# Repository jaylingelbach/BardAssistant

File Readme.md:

# BardAssistant – The Bard’s Assistant (ESP32-S3)

A tiny “Vicious Mockery” companion built on an ESP32-S3 DevKitM-1.

Right now it:

- Uses **buttons** to request insults (`Random`, `Next`, `Prev`, `Sleep (hold)`).
- Uses a **NeoPixel** as a simple state indicator:
  - **Blue** – Booting
  - **Green** – Idle (ready for button presses)
  - **Yellow** – Updating (pretending to “do work”)
  - **Magenta ** – Updating
- Prints insults and status info over **Serial** (`115200` baud).

Planned:

- Add a **Waveshare 2.13" E-Ink** screen and render insults + header there.
- Power stuff / sleep / wake on long-press.

---

## Hardware

Current setup:

- **Board**: ESP32-S3 DevKitM-1
- **LED**:
  - 1x NeoPixel RGB LED
  - Data pin: `GPIO 21`
- **Buttons** (tactile switches to GND, using `INPUT_PULLUP` in code):
  - Random: `GPIO 4`
  - Next: `GPIO 5`
  - Prev: `GPIO 6`
  - Sleep: `GPIO 7`

Planned display (not wired/used yet):

- Waveshare 2.13" E-Ink Display HAT V4
  - 250x122, SPI, partial refresh
  - Will eventually show:
    - Title screen / logo
    - Current insult text
    - Basic “source” info (`Random / Next / Prev`)

---

## Firmware Overview

All of this lives in `src/main.cpp` for now, plus small modules:

- `lib/button/` – debounced button input
- `lib/led/` – NeoPixel status LED

### Application States

```cpp
enum class ApplicationState { Boot, Idle, Updating };
```

- **Boot**
  - LED: Blue (`ledShowBoot()`)
  - After ~2 seconds, transitions to **Idle**

- **Idle**
  - LED: Green (`ledShowIdle()`)
  - Listens for button taps:
    - Random → start a “Random insult” operation
    - Next → move forward through insult history (or draw new)
    - Prev → move backward through insult history

- **Updating**
  - LED: Yellow (`ledShowUpdating()`)
  - Simulates “work” with a small delay (`MOCK_WORK_MS`)
  - When “done”, applies the insult index and goes back to Idle

### Buttons & Events

Buttons are debounced and produce high-level events (from `button` module):

```cpp
enum class ButtonEvent { None, Tap, HoldStart, HoldEnd };
```

- Tap → triggers Random / Next / Prev operations _while in Idle_
- Sleep:
  - `HoldStart` is wired to eventually trigger deep sleep (`enterSleep()`),
    currently just logs.

### Insults, Deck, and History (Serial Only for Now)

- `insults[]` – array of `const char*` insult strings.
- **Deck**:
  - Shuffled list of indices, ensures “Random” doesn’t repeat until all have been used.

- **History**:
  - Remembers which insults have been shown.
  - `Next` / `Prev` navigate the history when possible.
  - `Next` at the end of history draws a new insult from the deck.

Rendering is currently:

- `renderTitleScreen()` – ASCII art + project name on boot (Serial only).
- `renderInsultAtIndex(...)` – logs:
  - Which insult index is active
  - The insult text itself
  - Optional context (`Random` vs `Next` vs `Prev`)

Later, these will be redirected to the E-Ink screen instead of (or in addition to) Serial.

---

## PlatformIO – Commands I Keep Forgetting

> All commands assume you’re in the project root (where `platformio.ini` lives).

### Build

**Generic:**

```bash
pio run
```

**Specific environment (ESP32-S3 DevKitM-1):**

```bash
pio run -e esp32-s3-devkitm-1
```

---

### Upload Firmware

**Generic upload for default env:**

```bash
pio run -t upload
```

**Upload to ESP32-S3 DevKitM-1 explicitly:**

```bash
pio run -e esp32-s3-devkitm-1 -t upload
```

---

### Erase Flash

Useful when things get weird or after changing flash layout / partitions:

```bash
pio run -e esp32-s3-devkitm-1 -t erase
```

Then re-upload your firmware.

---

### Clean Build Artifacts

If builds start acting cursed:

```bash
pio run -t clean
```

---

### Serial Monitor

**On my Mac / current setup:**

```bash
pio device monitor -p /dev/cu.usbmodem1101 -b 115200
```

Generic form:

```bash
pio device monitor -p <PORT> -b 115200
```

Hit `Ctrl + C` to exit.

---

## Development Notes

- Buttons are wired **to GND** and use `INPUT_PULLUP`:
  - Released → HIGH
  - Pressed → LOW

- Long-press on Sleep is **debounced and recognized**.
- State machine and insult logic are conceptually separate:
  - `main.cpp` handles:
    - Board setup
    - State transitions
    - Calling “work engine” functions

- Insult/deck/history logic lives in `lib/insults/`

---

## Sleep / Wake Behavior

### Entering Sleep

1. **Hold** the Sleep button to arm sleep mode (LED turns magenta).
2. **Release** the button to enter deep sleep.

This "hold to sleep, release to confirm" gesture prevents accidental sleep entry.

### Waking Up

1. **Tap** or **press** the Sleep button while asleep — the pin goes LOW and triggers a wake.
2. The ESP32-S3 boots from reset and runs `setup()` again.
3. Optionally, wake reason can be detected via `esp_sleep_get_wakeup_cause()`.

## Setup (Fresh Clone)

```bash
# Clone
git clone https://github.com/jaylingelbach/BardAssistant.git
cd BardAssistant

# Build (default env)
pio run

# Or build for the ESP32-S3 env explicitly
pio run -e esp32-s3-devkitm-1

# Upload
pio run -e esp32-s3-devkitm-1 -t upload

# Monitor
pio device monitor -p /dev/cu.usbmodem1101 -b 115200
```

## Current display panel being used

- GxEPD2_213_B74

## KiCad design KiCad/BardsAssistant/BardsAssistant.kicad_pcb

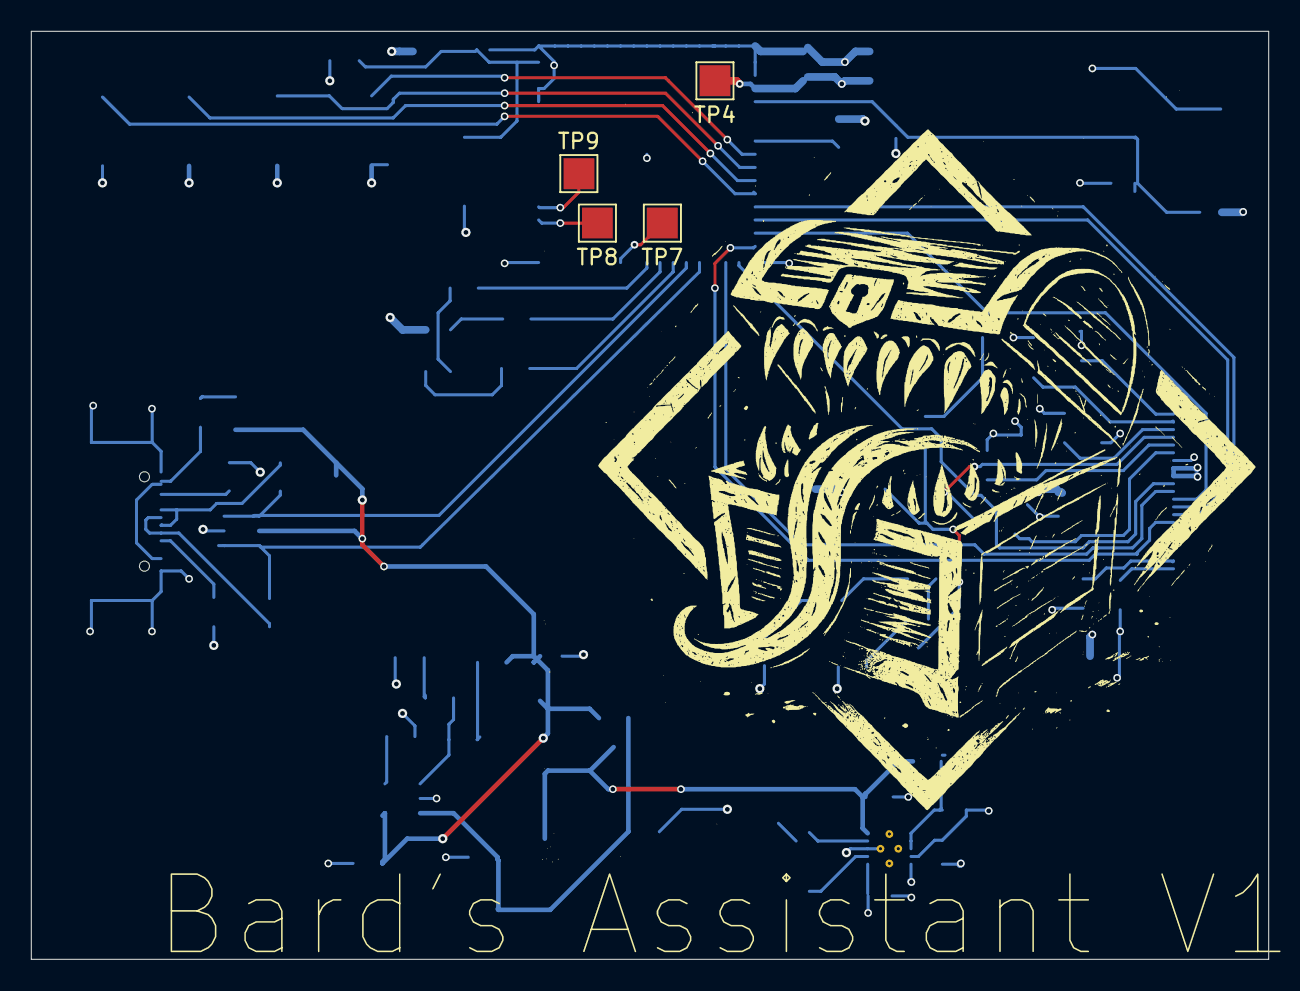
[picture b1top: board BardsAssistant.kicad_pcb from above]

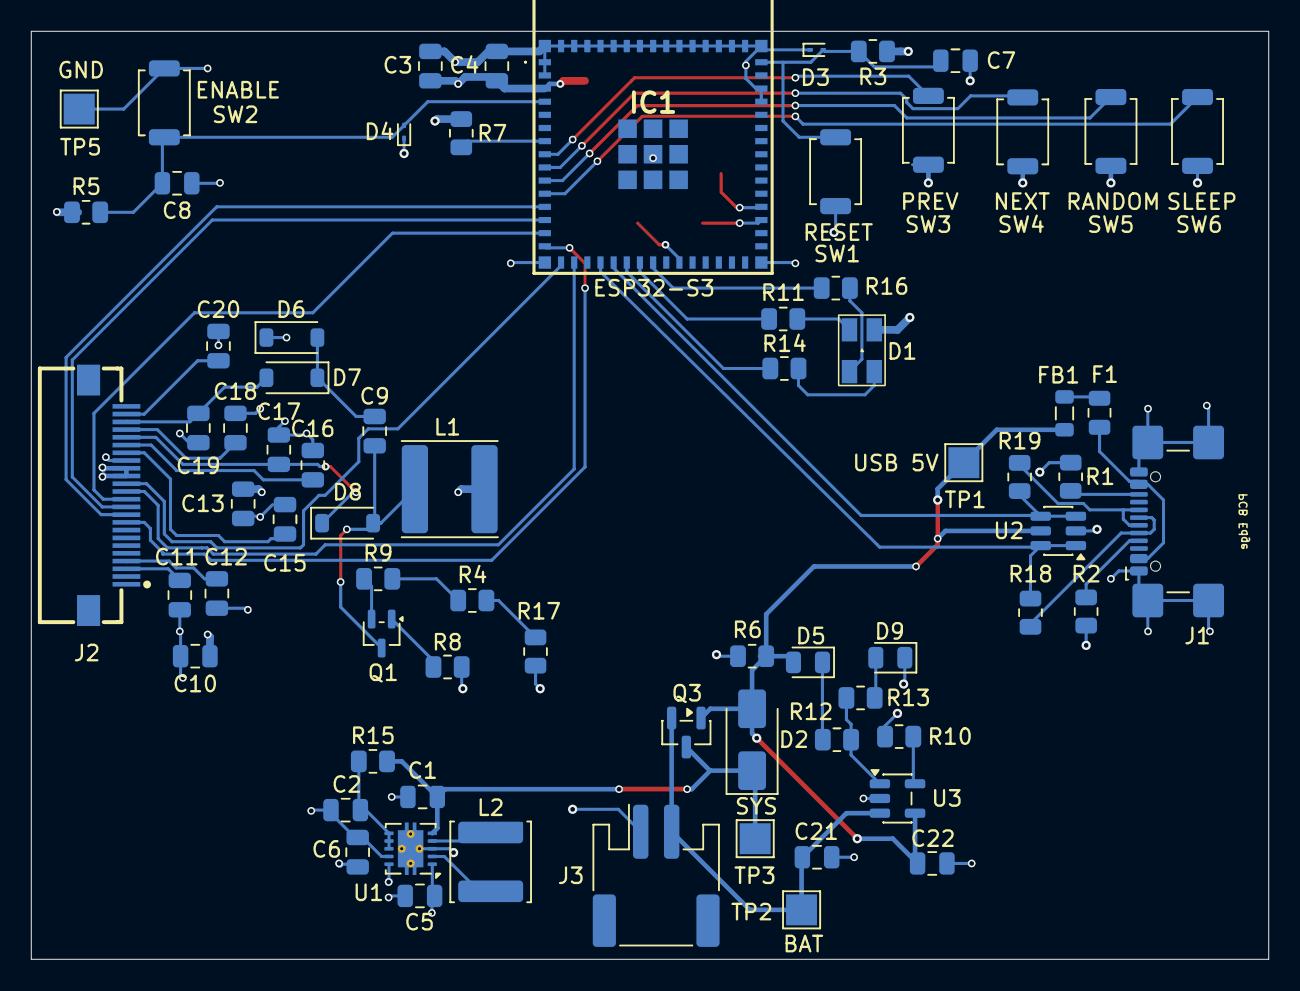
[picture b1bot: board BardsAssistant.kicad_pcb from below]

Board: 4 copper layers, 80.0 x 60.0 mm, 76 parts (72 on the bottom side), 56 nets.

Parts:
C1, C5, C6, C21, C22: 10uF; C_0805_2012Metric
C2, C4: .1uF; C_0805_2012Metric
C3: 22uF; C_0805_2012Metric
C7, C8, C11, C12, C13, C15, C16, C17, C18, C19, C20: 1uF; C_0805_2012Metric
C9, C10: 4.7uF; C_0805_2012Metric
D1: SM1210RGB; LED_XL-3227RGB-RF
D2: SS114; D_SMA
D3, D4: ESD9B3.3; D_SOD-923
D5: LED Red; LED_0805_2012Metric
D6, D7, D8: MBR0530; D_SOD-123
D9: LED Green; LED_0805_2012Metric
F1: Polyfuse 1A; Fuse_0805_2012Metric
FB1: BLM21PG221; L_0805_2012Metric
IC1: ESP32-S3-MINI-1-N8; ESP32S3MINI1N8
J1: USB_C_Receptacle_USB2.0_16P; USB_C_Receptacle_GCT_USB4110
J2: Conn_01x24; FPC-SMD_KH-FG0.5-H2.0-24PIN
J3: JST-PH-2-SMT-RA; JST_PH_S2B-PH-SM4-TB_1x02-1MP_P2.00mm_Horizontal
L1: 68uH; L_Sunlord_SWPA6045S
L2: 2.2uH; SMNR5040_2R2MT_BA
Q1: Si1308EDL; SOT-323_SC-70
Q3: AO3401A; SOT-23
R1, R2, R10: 5K1; R_0805_2012Metric
R3, R5, R7, R8: 10K; R_0805_2012Metric
R4, R9, R17: 1R; R_0805_2012Metric
R6: 100K; R_0805_2012Metric
R11, R14, R16: 330R; R_0805_2012Metric
R12, R13: 470R; R_0805_2012Metric
R15: 100R; R_0805_2012Metric
R18, R19: 22R; R_0805_2012Metric
SW1, SW2, SW3, SW4, SW5, SW6: SW_Push; SW_SPST_TS-1088-xR020
TP1, TP2, TP3, TP4, TP7, TP8, TP9: TestPoint; TestPoint_Pad_2.0x2.0mm
TP5: GND; TestPoint_Pad_2.0x2.0mm
U1: TPS63001; Texas_DRC0010J_ThermalVias
U2: USBLC6-2SC6; SOT-23-6
U3: MCP73831/2; SOT-23-5

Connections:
+3V3: C3.1, C4.1, C5.2, C6.2, C10.2, C13.2, D1.1 (A), IC1.3 (3V3), J2.15 (VDDIO), J2.16 (VCI), L1.1, R3.1, R5.1, R7.1, TP4.1, U1.1 (VOUT), U1.10 (FB)
/BAT: C21.2, J3.2, Q3.2 (BAT), TP2.1, U3.3 (V_{BAT})
/BUSY: IC1.15 (IO11), J2.9 (BUSY)
/CS: IC1.14 (IO10), J2.12 (CS)
/D+: IC1.20 (IO16), R19.1, U2.3 (I/O2), U2.4 (I/O2)
/D-: IC1.19 (IO15), R18.1, U2.1 (I/O1), U2.6 (I/O1)
/DC: IC1.13 (IO9), J2.11 (D/C)
/GDR: Q1.1 (G), R8.2
/MOSI: IC1.16 (IO12), J2.14 (SDI)
/PREVGH: C17.2, D8.1 (K), J2.20 (VSH)
/PREVGL: C19.2, D7.2 (A), J2.22 (VSL)
/RESE: Q1.2 (S), R9.1
/RST: IC1.12 (IO8), J2.10 (RST)
/SCK: IC1.17 (IO13), J2.13 (SCLK)
/SYS: C1.2, D2.1 (K), Q3.3 (SYS), R15.2, TP3.1, U1.5 (VIN)
/USB_5V: C22.2, D2.2 (A), D5.2 (A), FB1.2, Q3.1 (G), R6.2, TP1.1, U2.5 (VBUS), U3.4 (V_{DD})
GND: C1.1, C2.1, C3.2, C4.2, C5.1, C6.1, C7.2, C8.2, C10.1, C11.1, C12.1, C13.1, C15.1, C16.1, C17.1, C18.1, C19.1, C20.1, C21.1, C22.1, D3.1 (A1), D4.1 (A1), D6.1 (K), D9.1 (K), IC1.1 (GND_1), IC1.2 (GND_2), IC1.42 (GND_3), IC1.43 (GND_4), IC1.46 (GND_5), IC1.47 (GND_6), IC1.48 (GND_7), IC1.49 (GND_8), IC1.50 (GND_9), IC1.51 (GND_10), IC1.52 (GND_11), IC1.53 (GND_12), IC1.54 (GND_13), IC1.55 (GND_14), IC1.56 (GND_15), IC1.57 (GND_16), IC1.58 (GND_17), IC1.59 (GND_18), IC1.60 (GND_19), IC1.61 (GND_20), IC1.62 (GND_21), IC1.63 (GND_22), IC1.64 (GND_23), IC1.65 (GND_24), J1.A1 (GND), J1.A12 (GND), J1.B1 (GND), J1.B12 (GND), J1.S1 (SHIELD), J2.17 (VSS), J3.1, R1.1, R2.1, R6.1, R8.1, R10.2, R17.2, SW1.2, SW2.2, SW3.2, SW4.2, SW5.2, SW6.2, TP5.1, U1.3 (PGND), U1.9 (GND), U1.11 (PGND), U2.2 (GND), U3.2 (V_{SS})
unnamed: D1.4 (BK), R16.1
unnamed: D1.3 (GK), R14.1
unnamed: D1.2 (RK), R11.1
unnamed: C7.1, D3.2 (A2), IC1.45 (EN), R3.2, SW1.1
unnamed: C8.1, D4.2 (A2), IC1.4 (IO0), R5.2, SW2.1
unnamed: D5.1 (K), R12.1
unnamed: C9.1, D6.2 (A), D7.1 (K)
unnamed: C9.2, D8.2 (A), L1.2, Q1.3 (D)
unnamed: D9.2 (A), R13.1
unnamed: F1.1, J1.A4 (VBUS), J1.A9 (VBUS), J1.B4 (VBUS), J1.B9 (VBUS)
unnamed: F1.2, FB1.1
unnamed: IC1.7 (IO3), R7.2
unnamed: IC1.8 (IO4), SW3.1
unnamed: IC1.9 (IO5), SW4.1
unnamed: IC1.10 (IO6), SW5.1
unnamed: IC1.11 (IO7), SW6.1
unnamed: IC1.21 (IO17), R14.2
unnamed: IC1.22 (IO18), R11.2
unnamed: IC1.23 (IO19), R16.2
unnamed: IC1.25 (IO21), TP7.1
unnamed: IC1.33 (IO37), TP8.1
unnamed: IC1.34 (IO38), TP9.1
unnamed: J1.A5 (CC1), R2.2
unnamed: J1.B5 (CC2), R1.2
unnamed: J1.A6 (D+), J1.B6 (D+), R19.2
unnamed: J1.A7 (D-), J1.B7 (D-), R18.2
unnamed: C18.2, J2.21 (PREVGH)
unnamed: C20.2, J2.23 (PREVGL)
unnamed: C11.2, J2.3 (RESE)
unnamed: C15.2, J2.18 (VDD)
unnamed: C12.2, J2.4 (VGL)
unnamed: C16.2, J2.19 (VPP)
unnamed: R4.1, R9.2
unnamed: R4.2, R17.1
unnamed: C2.2, R15.1, U1.6 (EN), U1.7 (PS/SYNC), U1.8 (VINA)
unnamed: L2.1, U1.4 (L1)
unnamed: L2.2, U1.2 (L2)
unnamed: R10.1, U3.5 (PROG)
unnamed: R12.2, R13.2, U3.1 (STAT)

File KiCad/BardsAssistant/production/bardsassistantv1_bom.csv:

Designator,Footprint,Quantity,Value,LCSC Part #
"C1, C5, C6",0603,3,10uF,C19702
"C10, C9",0805,2,4.7uF,C1779
"C11, C12, C15, C16, C17, C18, C19, C20",0805,8,1uF,C15849
"C13, C7, C8",0603,3,1uF,C15849
"C2, C4",0603,2,.1uF,C14663
"C21, C22",0805,2,10uF,C19702
C3,0805,1,22uF,C45783
D1,LED_XL-3227RGB-RF,1,XL-3227RGB-RF,C965844
D2,D_SMA,1,SS114,C2480
"D3, D4",D_SOD-923,2,ESD9B3.3,C96512
D5,0603,1,LED Red,C2286
"D6, D7, D8",D_SOD-123,3,MBR0530,C77336
D9,0805,1,LED Green,C2297
F1,0805,1,Polyfuse 1A,C5307781
FB1,0805,1,BLM21PG221,C85840
IC1,ESP32S3MINI1N8,1,ESP32-S3-MINI-1-N8,C2913206
J1,USB_C_Receptacle_GCT_USB4110,1,USB_C_Receptacle_USB2.0_16P,C5143397
J2,FPC-SMD_KH-FG0.5-H2.0-24PIN,1,Conn_01x24,C2797213
J3,JST_PH_S2B-PH-SM4-TB_1x02-1MP_P2.00mm_Horizontal,1,JST-PH-2-SMT-RA,C157932
L1,L_Sunlord_SWPA6045S,1,68uH,C53663
L2,SMNR5040_2R2MT_BA,1,2.2uH,C9941
Q1,SOT-323_SC-70,1,Si1308EDL,C469327
Q3,SOT-23,1,AO3401A,C15127
"R1, R2",0402,2,5K1,C25905
R10,0402,1,5K,C25905
"R11, R14, R16",0402,3,330R,C23138
"R12, R13",0402,2,470R,C25117
R15,0402,1,100R,C25076
"R17, R4, R9",0603,3,1R,C22936
"R3, R5, R7, R8",0402,4,10K,C25744
R6,0402,1,100K,C25741
"SW1, SW2, SW3, SW4, SW5, SW6",SW_SPST_TS-1088-xR020,6,SW_Push,C720477
"TP1, TP2, TP3, TP4, TP7, TP8, TP9",TestPoint_Pad_2.0x2.0mm,7,TestPoint,
TP5,TestPoint_Pad_2.0x2.0mm,1,GND,
U1,Texas_DRC0010J_ThermalVias,1,TPS63001,C28060
U2,SOT-23-6,1,USBLC6-2SC6,C7519
U3,SOT-23-5,1,MCP73831/2,C424093

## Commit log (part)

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2025-12-25 init commit
2025-12-25 update gitignore
2025-12-26 Button and LED modules
2025-12-26 led and button modules
2025-12-26 Update main and platformio config
2025-12-26 Update main
2025-12-26 Fix include directive formatting in main.cpp
2025-12-26 remove redundent patterns
2025-12-26 remove outdated comment
2025-12-26 remove hardcoded ports
2025-12-26 move event handling outside of loop
2025-12-26 remove unused
2025-12-26 Group the API declaration
2025-12-26 📝 Add docstrings to `feature/led-module-fixed`
    Docstrings generation was requested by @jaylingelbach.
    * https://github.com/jaylingelbach/BardAssistant/pull/1#issuecomment-3693447027
    The following files were modified:
    * `lib/button/button.cpp`
    * `lib/led/led.cpp`
    * `src/main.cpp`
2025-12-27 adjust led brightness
2025-12-27 deck and history helpers
2025-12-27 render insults via serial
2025-12-27 remove redundent checks
2025-12-27 📝 Add docstrings to `feature/render-insults-serial`
    Docstrings generation was requested by @jaylingelbach.
    * https://github.com/jaylingelbach/BardAssistant/pull/3#issuecomment-3694201604
    The following files were modified:
    * `lib/led/led.cpp`
    * `src/main.cpp`
2025-12-27 insults module
2025-12-27 Add diagnostic when history is full.
2025-12-28 Minimal ring buffer to support prev/next cursor semantics
2025-12-28 cleaup dead branch of code and fix docstring
2025-12-28 update comment
2025-12-28 Enter and wake from sleep
2025-12-28 Restore LED state when sleep is cancelled.
2025-12-28 if error in wakeup, log.
2025-12-28 error handling for sleep
2025-12-29 Add wake from deep sleep and restore state
2025-12-29 Update to use preprocessor macro for enabling logs
2025-12-29 Refactor nvs key to shared header
2025-12-29 fix compilation error
2025-12-29 update comments
2026-01-03 Display firmware display.h & .cpp
2026-01-03 Ignore and remove clangd cache files
2026-01-03 use quotes for local import
2026-01-03 fix early return
2026-01-03 remove unused dep
2026-01-03 pinned dep
